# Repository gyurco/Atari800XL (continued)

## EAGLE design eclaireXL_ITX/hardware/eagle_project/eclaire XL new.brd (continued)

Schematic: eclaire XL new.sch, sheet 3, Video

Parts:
C10, C11: 0.1uF; C0805
HDMI: HDMI
JP2: JP2E; JP2
R5: 348; M0805
R6, R7, R8: 75; M0805
R9, R10: 100; R0805
RN1, RN2: 270; 743-8
S-VIDEO_COMP: MD04SS; MDIN04SS
VGA: DB15
VIDEODACSA: U5; QFP50P900X900X120-49N

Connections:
3V3: C11.1, VIDEODACSA.13 (VAA_2), VIDEODACSA.29 (VAA_3), VIDEODACSA.30 (VAA), VIDEODACSA.38 (~PSAVE); also elsewhere on the board
5V0: HDMI.18 (+5V); also elsewhere on the board
GND: C10.2, HDMI.2 (GND), HDMI.5 (GND), HDMI.8 (GND), HDMI.11 (GND), HDMI.17 (GND), HDMI.P$1 (GND), HDMI.P$2 (GND), HDMI.P$3 (GND), HDMI.P$4 (GND), R5.1, R6.1, R7.1, R8.1, S-VIDEO_COMP.1, S-VIDEO_COMP.2, VGA.5, VGA.6, VGA.7, VGA.8, VGA.10, VIDEODACSA.1 (GND_2), VIDEODACSA.2 (GND_3), VIDEODACSA.12 (~SYNC), VIDEODACSA.14 (GND_4), VIDEODACSA.15 (GND_5), VIDEODACSA.25 (GND_6), VIDEODACSA.26 (GND_7), VIDEODACSA.27 (~IOB), VIDEODACSA.31 (~IOG), VIDEODACSA.33 (~IOR), VIDEODACSA.39 (GND_8), VIDEODACSA.40 (GND); also elsewhere on the board
HSYNC: R10.1; also elsewhere on the board
unnamed: R9.2, VGA.14
unnamed: R10.2, VGA.13
unnamed: JP2.3, R6.2, VGA.1, VIDEODACSA.34 (IOR)
unnamed: R7.2, S-VIDEO_COMP.4, VGA.2, VIDEODACSA.32 (IOG)
unnamed: C10.1, VIDEODACSA.36 (VREF)
unnamed: R5.2, VIDEODACSA.37 (RSET)
unnamed: C11.2, VIDEODACSA.35 (COMP)
unnamed: HDMI.1 (TX2_P), RN1.8
unnamed: JP2.1, R8.2, VGA.3, VIDEODACSA.28 (IOB)
unnamed: HDMI.3 (TX2_N), RN1.7
unnamed: HDMI.4 (TX1_P), RN1.6
unnamed: HDMI.6 (TX1_N), RN1.5
unnamed: HDMI.7 (TX0_P), RN2.8
unnamed: HDMI.9 (TX0_N), RN2.7
unnamed: HDMI.10 (CLK_P), RN2.6
unnamed: HDMI.12 (CLK_N), RN2.5
unnamed: JP2.2, S-VIDEO_COMP.3
VGA_B0: VIDEODACSA.16 (B0); also elsewhere on the board
VGA_B1: RN2.2, VIDEODACSA.17 (B1); also elsewhere on the board
VGA_B2: VIDEODACSA.18 (B2); also elsewhere on the board
VGA_B3: VIDEODACSA.19 (B3); also elsewhere on the board
VGA_B4: RN2.1, VIDEODACSA.20 (B4); also elsewhere on the board
VGA_B5: RN2.4, VIDEODACSA.21 (B5); also elsewhere on the board
VGA_B6: RN2.3, VIDEODACSA.22 (B6); also elsewhere on the board
VGA_B7: VIDEODACSA.23 (B7); also elsewhere on the board
VGA_BLANK_N: VIDEODACSA.11 (~BLANK); also elsewhere on the board
VGA_CLK: VIDEODACSA.24 (CLOCK); also elsewhere on the board
VGA_G0: VIDEODACSA.3 (G0); also elsewhere on the board
VGA_G1: VIDEODACSA.4 (G1); also elsewhere on the board
VGA_G2: VIDEODACSA.5 (G2); also elsewhere on the board
VGA_G3: VIDEODACSA.6 (G3); also elsewhere on the board
VGA_G4: VIDEODACSA.7 (G4); also elsewhere on the board
VGA_G5: VIDEODACSA.8 (G5); also elsewhere on the board
VGA_G6: VIDEODACSA.9 (G6); also elsewhere on the board
VGA_G7: VIDEODACSA.10 (G7); also elsewhere on the board
VGA_R0: RN1.1, VIDEODACSA.41 (R0); also elsewhere on the board
VGA_R1: RN1.2, VIDEODACSA.42 (R1); also elsewhere on the board
VGA_R2: VIDEODACSA.43 (R2); also elsewhere on the board
VGA_R3: RN1.4, VIDEODACSA.44 (R3); also elsewhere on the board
VGA_R4: RN1.3, VIDEODACSA.45 (R4); also elsewhere on the board
VGA_R5: VIDEODACSA.46 (R5); also elsewhere on the board
VGA_R6: VIDEODACSA.47 (R6); also elsewhere on the board
VGA_R7: VIDEODACSA.48 (R7); also elsewhere on the board
VSYNC: R9.1; also elsewhere on the board

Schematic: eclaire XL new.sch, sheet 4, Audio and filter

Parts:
AC97_AUDIO: ML10
C21, C24: 100uF; C1206
C22, C23, C25, C26: 10nF; C0805
J3: AUDIO-JACK2CUI; AUDIO-JACK-CUI-353X
R35, R36, R37, R38: 560; M0805
R39: 1k; M0805

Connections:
AUDIO_LEFT: R38.2; also elsewhere on the board
AUDIO_RIGHT: R36.2; also elsewhere on the board
GND: AC97_AUDIO.2, C22.2, C23.2, C25.1, C26.1, J3.P$1 (SLEEVE); also elsewhere on the board
MIC_AC97: AC97_AUDIO.1; also elsewhere on the board
unnamed: C21.2, C22.1, R35.1
unnamed: C23.1, R35.2, R36.1, R39.2
unnamed: C26.2, R37.2, R38.1, R39.1
unnamed: AC97_AUDIO.9, C24.1, J3.P$2 (TIP)
unnamed: AC97_AUDIO.5, C21.1, J3.P$3 (RING)
unnamed: C24.2, C25.2, R37.1

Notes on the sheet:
Filter for delta sigma audio dac

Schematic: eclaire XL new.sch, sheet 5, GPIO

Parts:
GPIO_A: ML40E; ML40
GPIO_B: ML14
RN13, RN14, RN15, RN16, RN17, RN18, RN19, RN20, RN21, RN26, RN27, RN28: 100; 743-8
U$5: HDR_SMALL_36_DEV_LALIGNED; HDR_141_36

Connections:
3V3: GPIO_A.29, GPIO_B.13; also elsewhere on the board
5V0: GPIO_A.11, GPIO_B.14; also elsewhere on the board
EXP1: GPIO_B.1, RN26.6
EXP2: GPIO_B.2, RN26.5
EXP3: GPIO_B.3, RN27.8
EXP4: GPIO_B.4, RN27.7
EXP5: GPIO_B.5, RN27.6
EXP6: GPIO_B.6, RN27.5
EXP7: GPIO_B.7, RN28.8
EXP8: GPIO_B.8, RN28.7
EXP9: GPIO_B.9, RN28.6
EXP10: GPIO_B.10, RN28.5
GND: GPIO_A.12, GPIO_A.30, GPIO_B.11, GPIO_B.12; also elsewhere on the board
GPIOA0: RN13.1, U$5.P$1 (GPIO_0); also elsewhere on the board
GPIOA1: RN13.2, U$5.P$2 (GPIO_1); also elsewhere on the board
GPIOA2: RN13.3, U$5.P$3 (GPIO_2); also elsewhere on the board
GPIOA3: RN13.4, U$5.P$4 (GPIO_3); also elsewhere on the board
GPIOA4: RN14.1, U$5.P$5 (GPIO_4); also elsewhere on the board
GPIOA5: RN14.2, U$5.P$6 (GPIO_5); also elsewhere on the board
GPIOA6: RN14.3, U$5.P$7 (GPIO_6); also elsewhere on the board
GPIOA7: RN14.4, U$5.P$8 (GPIO_7); also elsewhere on the board
GPIOA8: RN15.1, U$5.P$9 (GPIO_8); also elsewhere on the board
GPIOA9: RN15.2, U$5.P$10 (GPIO_9); also elsewhere on the board
GPIOA10: RN15.3, U$5.P$11 (GPIO_10); also elsewhere on the board
GPIOA11: RN15.4, U$5.P$12 (GPIO_11); also elsewhere on the board
GPIOA12: RN16.1, U$5.P$13 (GPIO_12); also elsewhere on the board
GPIOA13: RN16.2, U$5.P$14 (GPIO_13); also elsewhere on the board
GPIOA14: RN16.3, U$5.P$15 (GPIO_14); also elsewhere on the board
GPIOA15: RN16.4, U$5.P$16 (GPIO_15); also elsewhere on the board
GPIOA16: RN17.1, U$5.P$17 (GPIO_16); also elsewhere on the board
GPIOA17: RN17.2, U$5.P$18 (GPIO_17); also elsewhere on the board
GPIOA18: RN17.3, U$5.P$19 (GPIO_18); also elsewhere on the board
GPIOA19: RN17.4, U$5.P$20 (GPIO_19); also elsewhere on the board
GPIOA20: RN18.1, U$5.P$21 (GPIO_20); also elsewhere on the board
GPIOA21: RN18.2, U$5.P$22 (GPIO_21); also elsewhere on the board
GPIOA22: RN18.3, U$5.P$23 (GPIO_22); also elsewhere on the board
GPIOA23: RN18.4, U$5.P$24 (GPIO_23); also elsewhere on the board
GPIOA24: RN19.1, U$5.P$25 (GPIO_24); also elsewhere on the board
GPIOA25: RN19.2, U$5.P$26 (GPIO_25); also elsewhere on the board
GPIOA26: RN19.3, U$5.P$27 (GPIO_26); also elsewhere on the board
GPIOA27: RN19.4, U$5.P$28 (GPIO_27); also elsewhere on the board
GPIOA28: RN20.1, U$5.P$29 (GPIO_28); also elsewhere on the board
GPIOA29: RN20.2, U$5.P$30 (GPIO_29); also elsewhere on the board
GPIOA30: RN20.3, U$5.P$31 (GPIO_30); also elsewhere on the board
GPIOA31: RN20.4, U$5.P$32 (GPIO_31); also elsewhere on the board
GPIOA32: RN21.1, U$5.P$33 (GPIO_32); also elsewhere on the board
GPIOA33: RN21.2, U$5.P$34 (GPIO_33); also elsewhere on the board
GPIOA34: RN21.3, U$5.P$35 (GPIO_34); also elsewhere on the board
GPIOA35: RN21.4, U$5.P$36 (GPIO_35); also elsewhere on the board
GPIOB8: RN26.1; also elsewhere on the board
GPIOB9: RN26.2; also elsewhere on the board
GPIOB10: RN26.3; also elsewhere on the board
GPIOB11: RN26.4; also elsewhere on the board
GPIOB12: RN27.1; also elsewhere on the board
GPIOB13: RN27.2; also elsewhere on the board
GPIOB14: RN27.3; also elsewhere on the board
GPIOB15: RN27.4; also elsewhere on the board
GPIOC16: RN28.2; also elsewhere on the board
GPIOC17: RN28.1; also elsewhere on the board
GPIOC18: RN28.3; also elsewhere on the board
GPIOC19: RN28.4; also elsewhere on the board
unnamed: GPIO_A.1, RN13.8
unnamed: GPIO_A.2, RN13.7
unnamed: GPIO_A.3, RN13.6
unnamed: GPIO_A.4, RN13.5
unnamed: GPIO_A.5, RN14.8
unnamed: GPIO_A.6, RN14.7
unnamed: GPIO_A.7, RN14.6
unnamed: GPIO_A.8, RN14.5
unnamed: GPIO_A.9, RN15.8
unnamed: GPIO_A.10, RN15.7
unnamed: GPIO_A.13, RN15.6
unnamed: GPIO_A.14, RN15.5
unnamed: GPIO_A.15, RN16.8
unnamed: GPIO_A.17, RN16.6
unnamed: GPIO_A.16, RN16.7
unnamed: GPIO_A.18, RN16.5
unnamed: GPIO_A.19, RN17.8
unnamed: GPIO_A.20, RN17.7
unnamed: GPIO_A.21, RN17.6
unnamed: GPIO_A.22, RN17.5
unnamed: GPIO_A.23, RN18.8
unnamed: GPIO_A.25, RN18.6
unnamed: GPIO_A.24, RN18.7
unnamed: GPIO_A.26, RN18.5
unnamed: GPIO_A.27, RN19.8
unnamed: GPIO_A.28, RN19.7
unnamed: GPIO_A.31, RN19.6
unnamed: GPIO_A.32, RN19.5
unnamed: GPIO_A.33, RN20.8
unnamed: GPIO_A.34, RN20.7
unnamed: GPIO_A.35, RN20.6
unnamed: GPIO_A.36, RN20.5
unnamed: GPIO_A.37, RN21.8
unnamed: GPIO_A.38, RN21.7
unnamed: GPIO_A.39, RN21.6
unnamed: GPIO_A.40, RN21.5
SER2: RN26.8; also elsewhere on the board
SER3: RN26.7; also elsewhere on the board

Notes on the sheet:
Resistors!!

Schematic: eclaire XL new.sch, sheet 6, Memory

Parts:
C19: 0.1uF; C0805
SDRAM: U8; TSOP54

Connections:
3V3: C19.1, SDRAM.1 (VDD), SDRAM.3 (VDDQ), SDRAM.9 (VDDQ), SDRAM.14 (VDD), SDRAM.27 (VDD), SDRAM.43 (VDDQ), SDRAM.49 (VDDQ); also elsewhere on the board
A0: SDRAM.23 (A0); also elsewhere on the board
A1: SDRAM.24 (A1); also elsewhere on the board
A2: SDRAM.25 (A2); also elsewhere on the board
A3: SDRAM.26 (A3); also elsewhere on the board
A4: SDRAM.29 (A4); also elsewhere on the board
A5: SDRAM.30 (A5); also elsewhere on the board
A6: SDRAM.31 (A6); also elsewhere on the board
A7: SDRAM.32 (A7); also elsewhere on the board
A8: SDRAM.33 (A8); also elsewhere on the board
A9: SDRAM.34 (A9); also elsewhere on the board
A10: SDRAM.22 (A10/AP); also elsewhere on the board
A11: SDRAM.35 (A11); also elsewhere on the board
A12: SDRAM.36 (A12); also elsewhere on the board
BA0: SDRAM.20 (BA0); also elsewhere on the board
BA1: SDRAM.21 (BA1); also elsewhere on the board
CAS_N: SDRAM.17 (CAS#); also elsewhere on the board
CKE: SDRAM.37 (CKE); also elsewhere on the board
CS_N: SDRAM.19 (CS#); also elsewhere on the board
DQ0: SDRAM.2 (DQ0); also elsewhere on the board
DQ1: SDRAM.4 (DQ1); also elsewhere on the board
DQ2: SDRAM.5 (DQ2); also elsewhere on the board
DQ3: SDRAM.7 (DQ3); also elsewhere on the board
DQ4: SDRAM.8 (DQ4); also elsewhere on the board
DQ5: SDRAM.10 (DQ5); also elsewhere on the board
DQ6: SDRAM.11 (DQ6); also elsewhere on the board
DQ7: SDRAM.13 (DQ7); also elsewhere on the board
DQ8: SDRAM.42 (DQ8); also elsewhere on the board
DQ9: SDRAM.44 (DQ9); also elsewhere on the board
DQ10: SDRAM.45 (DQ10); also elsewhere on the board
DQ11: SDRAM.47 (DQ11); also elsewhere on the board
DQ12: SDRAM.48 (DQ12); also elsewhere on the board
DQ13: SDRAM.50 (DQ13); also elsewhere on the board
DQ14: SDRAM.51 (DQ14); also elsewhere on the board
DQ15: SDRAM.53 (DQ15); also elsewhere on the board
GND: C19.2, SDRAM.6 (VSSQ), SDRAM.12 (VSSQ), SDRAM.28 (VSS), SDRAM.41 (VSS), SDRAM.46 (VSSQ), SDRAM.52 (VSSQ), SDRAM.54 (VSS); also elsewhere on the board
RAS_N: SDRAM.18 (RAS#); also elsewhere on the board
SDRAM_CLK: SDRAM.38 (CLK); also elsewhere on the board
SDRAM_LDQM: SDRAM.15 (LDQM); also elsewhere on the board
SDRAM_UDQM: SDRAM.39 (DQM); also elsewhere on the board
WE_N: SDRAM.16 (WE#); also elsewhere on the board

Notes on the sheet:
Standard 64 bit wide tssop 54 sram. One like de1 would be good.

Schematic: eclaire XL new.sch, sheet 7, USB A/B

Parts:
PF2: 500mA; R1206
R25, R27, R29, R31: 22; R0805
R26, R28, R30, R32: 15k; R0805
USB_A_B: ML10
X1, X3: USB-A-H

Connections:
5V0: PF2.1; also elsewhere on the board
GND: R26.2, R28.2, R30.2, R32.2, USB_A_B.7, USB_A_B.8, X1.GND, X3.GND; also elsewhere on the board
unnamed: PF2.2, USB_A_B.1, USB_A_B.2, X1.VBUS, X3.VBUS
unnamed: R25.2, R26.1, USB_A_B.5, X1.D+
unnamed: R27.2, R28.1, USB_A_B.3, X1.D-
unnamed: R29.2, R30.1, USB_A_B.6, X3.D+
unnamed: R31.2, R32.1, USB_A_B.4, X3.D-
USB1DM: R27.1; also elsewhere on the board
USB1DP: R25.1; also elsewhere on the board
USB2DM: R31.1; also elsewhere on the board
USB2DP: R29.1; also elsewhere on the board

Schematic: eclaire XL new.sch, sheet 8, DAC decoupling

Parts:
C12, C14: 0.1uF; C0805
C13: 0.01uF; C0805
C15: 10uF; C0805

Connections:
3V3: C12.1, C13.1, C14.1, C15.1; also elsewhere on the board
GND: C12.2, C13.2, C14.2, C15.2; also elsewhere on the board

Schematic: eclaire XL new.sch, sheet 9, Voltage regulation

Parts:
1.1V: U3; SOT95P280X145-5N
1V1: White; CHIP-LED0805
2.5V: U2; SOT95P280X145-5N
2V5: Green; CHIP-LED0805
3.3/2.5/1.1/GND: J2; 1X04
3.3V: U1; SOT95P280X145-5N
3V3: Red; CHIP-LED0805
C1, C2, C3, C4, C5: 10uF; C0805
C6, C7, C8: 22uF; C0805
C9: 15pF; C0805
L1, L2, L3: 1uH; L3225M
PF1: 1A; R1206
R1: 1k; R0805
R2: 4k7; R0805
R3: 200; R0805
R4: 240; R0805
R22: 82; R0805
R23, R24: 56; R0805
TR1: BC817-16LT1SMD; SOT23-BEC
U$6: MOLEX_PS

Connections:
1V1: 3.3/2.5/1.1/GND.3, C8.1, C9.1, L3.2, R4.2, TR1.B; also elsewhere on the board
2V5: 2.5V.4 (ADJ/BYP), 3.3/2.5/1.1/GND.2, C7.1, L2.2, R23.2; also elsewhere on the board
3V3: 3.3/2.5/1.1/GND.1, 3.3V.4 (ADJ/BYP), C6.1, L1.2, R22.2; also elsewhere on the board
5V0: 1.1V.1 (VIN), 1V1.A, 2.5V.1 (VIN), 3.3V.1 (VIN), C3.1, C4.1, C5.1, PF1.2, R1.1, R2.1; also elsewhere on the board
5V0FAST: 1.1V.3 (EN), C1.1, R1.2
5V0SLOW: 2.5V.3 (EN), 3.3V.3 (EN), C2.2, R2.2
GND: 1.1V.2 (GND), 2.5V.2 (GND), 2V5.C, 3.3/2.5/1.1/GND.4, 3.3V.2 (GND), 3V3.C, C1.2, C2.1, C3.2, C4.2, C5.2, C6.2, C7.2, C8.2, R3.1, R24.2, U$6.- (--); also elsewhere on the board
unnamed: PF1.1, U$6.+
unnamed: 3V3.A, R22.1
unnamed: 2V5.A, R23.1
unnamed: 1V1.C, TR1.C
unnamed: R24.1, TR1.E
unnamed: 1.1V.5 (VOUT), L3.1
unnamed: 2.5V.5 (VOUT), L2.1
unnamed: 3.3V.5 (VOUT), L1.1
unnamed: 1.1V.4 (ADJ/BYP), C9.2, R3.2, R4.1

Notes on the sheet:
TODO: RC delay calc

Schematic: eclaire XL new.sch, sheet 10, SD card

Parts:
R40, R41, R42: 47K; M0805
SD: SDSOCKET

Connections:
3V3: R40.2, R41.2, R42.2, SD.4 (3V3); also elsewhere on the board
GND: SD.3 (GND), SD.6 (GND2), SD.10 (GP1), SD.11 (GP2); also elsewhere on the board
SD_CS: R40.1, SD.1 (CS); also elsewhere on the board
SD_DAT1: SD.8 (DAT1); also elsewhere on the board
SD_DAT2: SD.9 (DAT2); also elsewhere on the board
SD_DETECT: SD.3A (CARD_DET); also elsewhere on the board
SD_MISO: R42.1, SD.7 (DATA_OUT); also elsewhere on the board
SD_MOSI: R41.1, SD.2 (DATA_IN); also elsewhere on the board
SD_SCK: SD.5 (SCLK); also elsewhere on the board
SD_WRITEPROTECT: SD.8A (WRITE_PR); also elsewhere on the board

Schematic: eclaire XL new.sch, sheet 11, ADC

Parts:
ADC: U4; SOT95P280X145-5N
C16: 0.1uF; C0805
MIC_IN_SEL: J1; JP3Q
R11, R13: 2k; M0805

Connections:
3V3: ADC.1 (VCC), C16.1, R11.1, R13.2; also elsewhere on the board
GND: ADC.2 (VSS), C16.2; also elsewhere on the board
MIC_AC97: MIC_IN_SEL.2; also elsewhere on the board
MIC_IN: ADC.3 (AIN), MIC_IN_SEL.1, MIC_IN_SEL.3, MIC_IN_SEL.5
MIC_PBI: MIC_IN_SEL.6; also elsewhere on the board
MIC_SIO: MIC_IN_SEL.4; also elsewhere on the board
SCL: ADC.5 (SCL), R11.2; also elsewhere on the board
SDA: ADC.4 (SDA), R13.1; also elsewhere on the board

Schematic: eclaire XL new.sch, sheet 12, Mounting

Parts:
H1, H2, H3, H4, H5, H6, H7: MOUNT-PAD-ROUND3.6; 3,6-PAD

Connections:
GND: H1.B3,6, H2.B3,6, H3.B3,6, H4.B3,6, H5.B3,6, H6.B3,6, H7.B3,6; also elsewhere on the board

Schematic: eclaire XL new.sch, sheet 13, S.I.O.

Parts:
C20: 0.1uF; C0805K
D1: 1N4148; SOD123
PF3: 500mA; R1206
QS3384: U9; TSSOP24
R33, R34: 2k7; M0805
RN3, RN4: 100; 743-8
RN5, RN6: 4K7; 743-8
S.I.O._INTERFACE: ML10
TR2: MOT; SOT23-BEC

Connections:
5V0: D1.2 (AN), R33.1, RN5.1, RN5.2, RN5.3, RN5.4, RN6.1, RN6.2, RN6.3, RN6.4, TR2.E; also elsewhere on the board
COMMAND: RN4.2; also elsewhere on the board
GND: C20.2, QS3384.1 (BE), QS3384.12 (GND), QS3384.13 (BE), QS3384.20 (B), QS3384.21 (A), QS3384.22 (A), QS3384.23 (B); also elsewhere on the board
MIC_SIO: S.I.O._INTERFACE.9; also elsewhere on the board
MOTOR_RAW: RN3.1; also elsewhere on the board
unnamed: QS3384.3 (A), RN3.8
unnamed: QS3384.19 (B), RN5.6, S.I.O._INTERFACE.2
unnamed: QS3384.4 (A), RN3.7
unnamed: QS3384.7 (A), RN3.6
unnamed: QS3384.8 (A), RN3.5
unnamed: QS3384.11 (A), RN4.8
unnamed: QS3384.18 (A), RN4.7
unnamed: QS3384.17 (A), RN4.6
unnamed: QS3384.14 (A), RN4.5
unnamed: R34.2, TR2.B
unnamed: QS3384.16 (B), RN5.8, S.I.O._INTERFACE.4
unnamed: QS3384.15 (B), RN6.6, S.I.O._INTERFACE.6
unnamed: QS3384.10 (B), RN6.7, S.I.O._INTERFACE.7
unnamed: QS3384.9 (B), RN6.5, S.I.O._INTERFACE.5
unnamed: QS3384.6 (B), RN5.7, S.I.O._INTERFACE.3
unnamed: PF3.2, TR2.C
unnamed: QS3384.5 (B), RN5.5, S.I.O._INTERFACE.1
unnamed: QS3384.2 (B), R33.2, R34.1
unnamed: C20.1, D1.1 (CA), QS3384.24 (4V3)
unnamed: PF3.1, S.I.O._INTERFACE.8, S.I.O._INTERFACE.10
PROCEED: RN4.3; also elsewhere on the board
SIO_CLOCKIN: RN4.4; also elsewhere on the board
SIO_CLOCKOUT: RN3.2; also elsewhere on the board
SIO_IN: RN3.3; also elsewhere on the board
SIO_IRQ: RN3.4; also elsewhere on the board
SIO_OUT: RN4.1; also elsewhere on the board

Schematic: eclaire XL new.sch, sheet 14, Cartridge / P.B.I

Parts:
C38, C39, C40, C41: 0.1uF; C0805K
D3: 1N4148; SOD123
IC1: U14; TSSOP24
IC2: U15; TSSOP24
IC3: U16; TSSOP24
IC4: U17; TSSOP24
P.B.I._INTERFACE: ML40E; ML40
R50, R51: 10k; M0805
R52, R53, R54, R55: 4k7; M0805
RN29, RN30, RN31, RN32, RN33, RN34, RN35, RN36, RN37: 100; 743-8

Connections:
4V3_INT: C38.1, C39.1, C40.1, C41.1, D3.1 (CA), IC1.24 (4V3), IC2.24 (4V3), IC3.24 (4V3), IC4.24 (4V3)
5V0: D3.2 (AN), R52.1, R53.1, R54.1, R55.1; also elsewhere on the board
.A0: IC3.2 (B), P.B.I._INTERFACE.23
.A1: IC3.6 (B), P.B.I._INTERFACE.25
.A2: IC3.10 (B), P.B.I._INTERFACE.27
.A3: IC3.15 (B), P.B.I._INTERFACE.28
.A4: IC3.9 (B), P.B.I._INTERFACE.26
.A5: IC3.5 (B), P.B.I._INTERFACE.24
.A6: IC2.23 (B), P.B.I._INTERFACE.22
.A7: IC2.19 (B), P.B.I._INTERFACE.20
.A8: IC2.15 (B), P.B.I._INTERFACE.18
.A9: IC2.9 (B), P.B.I._INTERFACE.16
.A10: IC1.10 (B), P.B.I._INTERFACE.5
.A11: IC1.15 (B), P.B.I._INTERFACE.6
.A12: IC2.5 (B), P.B.I._INTERFACE.14
.A13: IC3.23 (B), P.B.I._INTERFACE.34
.A14: IC4.2 (B), P.B.I._INTERFACE.35
.A15: IC4.5 (B), P.B.I._INTERFACE.36
.CCTL_N: IC1.2 (B), P.B.I._INTERFACE.1
.D0: IC2.2 (B), P.B.I._INTERFACE.13
.D1: IC2.6 (B), P.B.I._INTERFACE.15
.D2: IC2.10 (B), P.B.I._INTERFACE.17
.D3: IC1.23 (B), P.B.I._INTERFACE.10
.D4: IC2.20 (B), P.B.I._INTERFACE.21
.D5: IC2.16 (B), P.B.I._INTERFACE.19
.D6: IC1.20 (B), P.B.I._INTERFACE.9
.D7: IC1.19 (B), P.B.I._INTERFACE.8
.EXTSEL_N: IC3.20 (B), P.B.I._INTERFACE.33, R52.2
.IRQ_N: IC4.10 (B), P.B.I._INTERFACE.39, R55.2
.MPD_N: IC4.6 (B), P.B.I._INTERFACE.37, R53.2
.PHI2: IC1.5 (B), P.B.I._INTERFACE.2
.RD4: IC3.16 (B), P.B.I._INTERFACE.31, R51.2
.RD5: IC1.6 (B), P.B.I._INTERFACE.3, R50.2
.REF_N: IC4.9 (B), P.B.I._INTERFACE.38, R54.2
.RST_N: IC4.15 (B), P.B.I._INTERFACE.40
.RW_N: IC1.9 (B), P.B.I._INTERFACE.4
.S4_N: IC3.19 (B), P.B.I._INTERFACE.32
.S5_N: IC1.16 (B), P.B.I._INTERFACE.7
GND: C38.2, C39.2, C40.2, C41.2, IC1.1 (BE), IC1.12 (GND), IC1.13 (BE), IC2.1 (BE), IC2.12 (GND), IC2.13 (BE), IC3.1 (BE), IC3.12 (GND), IC3.13 (BE), IC4.1 (BE), IC4.12 (GND), IC4.13 (BE), IC4.16 (B), IC4.17 (A), IC4.18 (A), IC4.19 (B), IC4.20 (B), IC4.21 (A), IC4.22 (A), IC4.23 (B), R50.1, R51.1; also elsewhere on the board
GPIOB16: RN30.1; also elsewhere on the board
GPIOB17: RN30.2; also elsewhere on the board
GPIOB18: RN30.3; also elsewhere on the board
GPIOB19: RN30.4; also elsewhere on the board
GPIOB20: RN31.1; also elsewhere on the board
GPIOB21: RN31.2; also elsewhere on the board
GPIOB22: RN31.3; also elsewhere on the board
GPIOB23: RN31.4; also elsewhere on the board
GPIOB24: RN32.1; also elsewhere on the board
GPIOB25: RN32.2; also elsewhere on the board
GPIOB26: RN32.3; also elsewhere on the board
GPIOB27: RN32.4; also elsewhere on the board
GPIOB28: RN33.1; also elsewhere on the board
GPIOB29: RN33.2; also elsewhere on the board
GPIOB30: RN33.3; also elsewhere on the board
GPIOB31: RN33.4; also elsewhere on the board
GPIOB32: RN34.1; also elsewhere on the board
GPIOB33: RN34.2; also elsewhere on the board
GPIOB34: RN34.3; also elsewhere on the board
GPIOB35: RN34.4; also elsewhere on the board
GPIOC20: RN29.1; also elsewhere on the board
GPIOC21: RN29.2; also elsewhere on the board
GPIOC22: RN29.3; also elsewhere on the board
GPIOC23: RN29.4; also elsewhere on the board
GPIOC24: RN35.1; also elsewhere on the board
GPIOC25: RN35.2; also elsewhere on the board
GPIOC26: RN35.3; also elsewhere on the board
GPIOC27: RN35.4; also elsewhere on the board
GPIOC28: RN36.1; also elsewhere on the board
GPIOC29: RN36.2; also elsewhere on the board
GPIOC30: RN36.3; also elsewhere on the board
GPIOC31: RN36.4; also elsewhere on the board
GPIOC32: RN37.1; also elsewhere on the board
GPIOC33: RN37.2; also elsewhere on the board
GPIOC34: RN37.3; also elsewhere on the board
GPIOC35: RN37.4; also elsewhere on the board
MIC_PBI: P.B.I._INTERFACE.29, P.B.I._INTERFACE.30; also elsewhere on the board
PIO1: IC1.3 (A), RN29.8
PIO2: IC1.4 (A), RN29.7
PIO3: IC1.7 (A), RN29.6
PIO4: IC1.8 (A), RN29.5
PIO5: IC1.11 (A), RN30.8
PIO6: IC1.14 (A), RN30.7
PIO7: IC1.17 (A), RN30.6
PIO8: IC1.18 (A), RN30.5
PIO9: IC1.21 (A), RN31.8
PIO10: IC1.22 (A), RN31.7
PIO11: IC2.3 (A), RN31.6
PIO12: IC2.4 (A), RN31.5
PIO13: IC2.7 (A), RN32.8
PIO14: IC2.8 (A), RN32.7
PIO15: IC2.11 (A), RN32.6
PIO16: IC2.14 (A), RN32.5
PIO17: IC2.17 (A), RN33.8
PIO18: IC2.18 (A), RN33.7
PIO19: IC2.21 (A), RN33.6
PIO20: IC2.22 (A), RN33.5
PIO21: IC3.3 (A), RN34.8
PIO22: IC3.4 (A), RN34.7
PIO23: IC3.7 (A), RN34.6
PIO24: IC3.8 (A), RN34.5
PIO25: IC3.11 (A), RN35.8
PIO26: IC3.14 (A), RN35.7
PIO27: IC3.17 (A), RN35.6
PIO28: IC3.18 (A), RN35.5
PIO29: IC3.21 (A), RN36.8
PIO30: IC3.22 (A), RN36.7
PIO31: IC4.3 (A), RN36.6
PIO32: IC4.4 (A), RN36.5
PIO33: IC4.7 (A), RN37.8
PIO34: IC4.8 (A), RN37.7
PIO35: IC4.11 (A), RN37.6
PIO36: IC4.14 (A), RN37.5

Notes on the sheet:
PBI CONNECTOR

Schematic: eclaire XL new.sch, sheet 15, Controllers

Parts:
74HCT03: U12; SO14
C28, C29A, C30A: 0.1uF; C0805K
C29, C30, C31, C32: 0.047uF; C0805K
D2: 1N4148; SOD123
IC5: U10; TSSOP24
JOY1: JOYSTICK1; M09HP
JOY2: JOYSTICK2; M09HP
LM339: U11; TSSOP-14
PF4: 500mA; R1206
R43, R44: 4.7k; M0805
R45: 1.2K; R0805
R46: 2.1K; R0805
RN7, RN10, RN12: 4K7; 743-8
RN8, RN9: 220; 743-8
RN11: 1K; 743-8
RN22, RN23, RN24, RN25: 100; 743-8

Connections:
3V3: R45.2, RN12.5, RN12.6, RN12.7, RN12.8; also elsewhere on the board
4V3_INT1: C28.2, D2.1 (CA), IC5.24 (4V3)
5V0: 74HCT03.14 (VCC), C29A.1, C30A.1, D2.2 (AN), LM339.3 (VCC), PF4.1, R43.2, R44.2, RN7.1, RN7.2, RN7.3, RN7.4, RN10.5, RN10.6, RN10.7, RN10.8; also elsewhere on the board
5V00: JOY1.7, JOY2.7, PF4.2
GND: 74HCT03.7 (GND), C28.1, C29.2, C29A.2, C30.2, C30A.2, C31.2, C32.2, IC5.1 (BE), IC5.12 (GND), IC5.13 (BE), JOY1.8, JOY2.8, LM339.12 (GND), R46.1; also elsewhere on the board
GPIOB0: RN24.1; also elsewhere on the board
GPIOB1: RN24.2; also elsewhere on the board
GPIOB2: RN24.3; also elsewhere on the board
GPIOB3: RN24.4; also elsewhere on the board
GPIOB4: RN25.1; also elsewhere on the board
GPIOB5: RN25.2; also elsewhere on the board
GPIOB6: RN25.3; also elsewhere on the board
GPIOB7: RN25.4; also elsewhere on the board
GPIOC8: RN22.1; also elsewhere on the board
GPIOC9: RN22.2; also elsewhere on the board
GPIOC10: RN22.3; also elsewhere on the board
GPIOC11: RN22.4; also elsewhere on the board
GPIOC12: RN23.1; also elsewhere on the board
GPIOC13: RN23.3; also elsewhere on the board
GPIOC14: RN23.2; also elsewhere on the board
GPIOC15: RN23.4; also elsewhere on the board
JIO1: IC5.3 (A), RN22.8
JIO2: IC5.4 (A), RN22.7
JIO3: IC5.7 (A), RN22.6
JIO4: IC5.8 (A), RN22.5
JIO5: IC5.11 (A), RN23.8
JIO6: IC5.21 (A), RN23.6
JIO7: IC5.22 (A), RN23.7
JIO8: IC5.18 (A), RN23.5
JIO9: IC5.17 (A), RN24.8
JIO10: IC5.14 (A), RN24.7
JIO11: LM339.1 (OUT), RN12.1, RN24.6
JIO12: LM339.2 (OUT), RN12.2, RN24.5
JIO13: LM339.14 (OUT), RN12.3, RN25.8
JIO14: LM339.13 (OUT), RN12.4, RN25.7
JIO15: 74HCT03.1 (I0), 74HCT03.2 (I1), 74HCT03.4 (I0), 74HCT03.5 (I1), 74HCT03.9 (I0), 74HCT03.10 (I1), 74HCT03.12 (I0), 74HCT03.13 (I1), RN25.6
unnamed: LM339.4 (-IN), LM339.6 (-IN), LM339.8 (-IN), LM339.10 (-IN), R45.1, R46.2
PORTA0: IC5.2 (B), RN7.5, RN8.4
PORTA1: IC5.5 (B), RN7.6, RN8.3
PORTA2: IC5.6 (B), RN7.7, RN8.2
PORTA3: IC5.9 (B), RN7.8, RN8.1
PORTA4: IC5.10 (B), RN9.4, RN10.1
PORTA5: IC5.15 (B), RN9.3, RN10.2
PORTA6: IC5.16 (B), RN9.2, RN10.3
PORTA7: IC5.19 (B), RN9.1, RN10.4
PORTA_PROT0: JOY1.1, RN8.5
PORTA_PROT1: JOY1.2, RN8.6
PORTA_PROT2: JOY1.3, RN8.7
PORTA_PROT3: JOY1.4, RN8.8
PORTA_PROT4: JOY2.1, RN9.5
PORTA_PROT5: JOY2.2, RN9.6
PORTA_PROT6: JOY2.3, RN9.7
PORTA_PROT7: JOY2.4, RN9.8
POT0: 74HCT03.3 (O), C29.1, LM339.5 (+IN), RN11.1
POT1: 74HCT03.6 (O), C30.1, LM339.7 (+IN), RN11.2
POT2: 74HCT03.8 (O), C32.1, LM339.9 (+IN), RN11.4
POT3: 74HCT03.11 (O), C31.1, LM339.11 (+IN), RN11.3
POTIN0: JOY1.9, RN11.7
POTIN1: JOY1.5, RN11.8
POTIN2: JOY2.9, RN11.5
POTIN3: JOY2.5, RN11.6
SER1: RN25.5; also elsewhere on the board
TRIG0: IC5.23 (B), JOY1.6, R43.1
TRIG1: IC5.20 (B), JOY2.6, R44.1

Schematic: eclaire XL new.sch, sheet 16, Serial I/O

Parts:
C33, C34, C35, C36: 1UF; C0805K
MAX232: U13; SO16L
R47, R48, R49: 330; M0805
RX: LEDCHIP-LED0805; CHIP-LED0805
TX: LEDCHIP-LED0805; CHIP-LED0805
X2: F09V

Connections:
3V3: MAX232.16 (VCC), RX.A, TX.A; also elsewhere on the board
GND: C34.2, C36.2, MAX232.15 (GND), X2.5; also elsewhere on the board
unnamed: R47.1, TX.C
unnamed: R48.1, RX.C
unnamed: C34.1, MAX232.2 (V+)
unnamed: C33.2, MAX232.3 (C1-)
unnamed: C35.2, MAX232.5 (C2-)
unnamed: C33.1, MAX232.1 (C1+)
unnamed: C35.1, MAX232.4 (C2+)
unnamed: C36.1, MAX232.6 (V-)
unnamed: MAX232.14 (T1OUT), X2.2
unnamed: MAX232.13 (R1IN), X2.3
unnamed: MAX232.7 (T2OUT), X2.8
unnamed: MAX232.12 (R1OUT), R48.2, R49.2
SER1: MAX232.10 (T2IN); also elsewhere on the board
SER2: MAX232.11 (T1IN), R47.2; also elsewhere on the board
SER3: R49.1; also elsewhere on the board

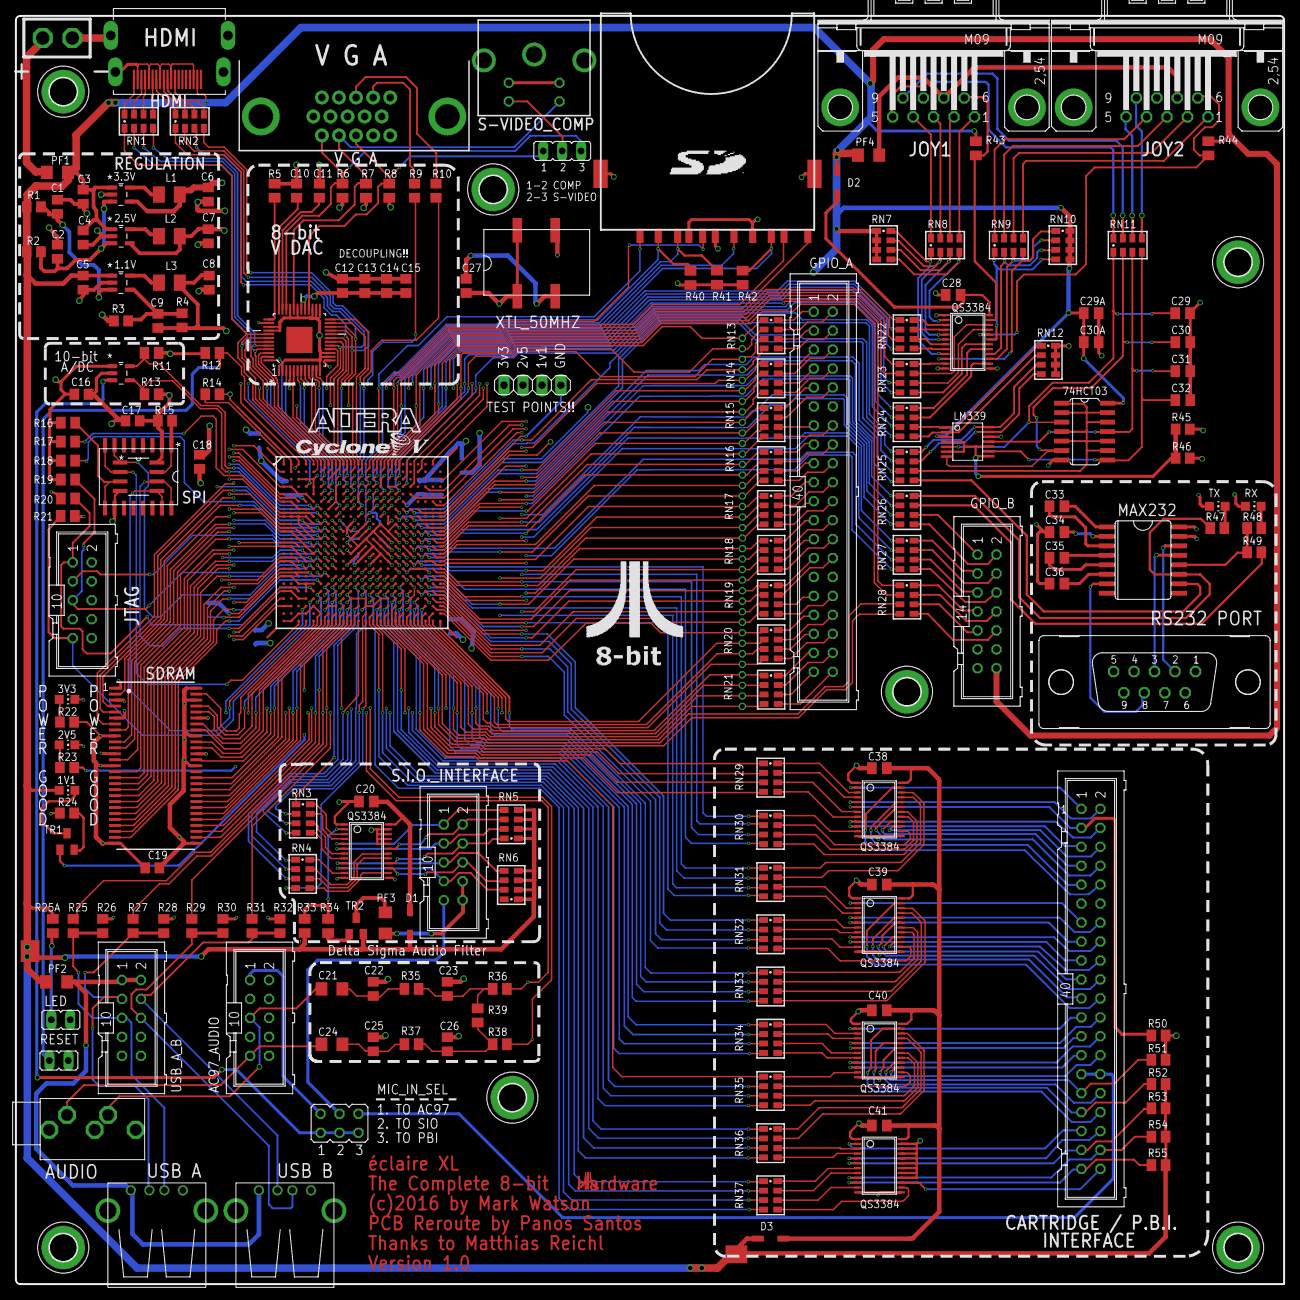
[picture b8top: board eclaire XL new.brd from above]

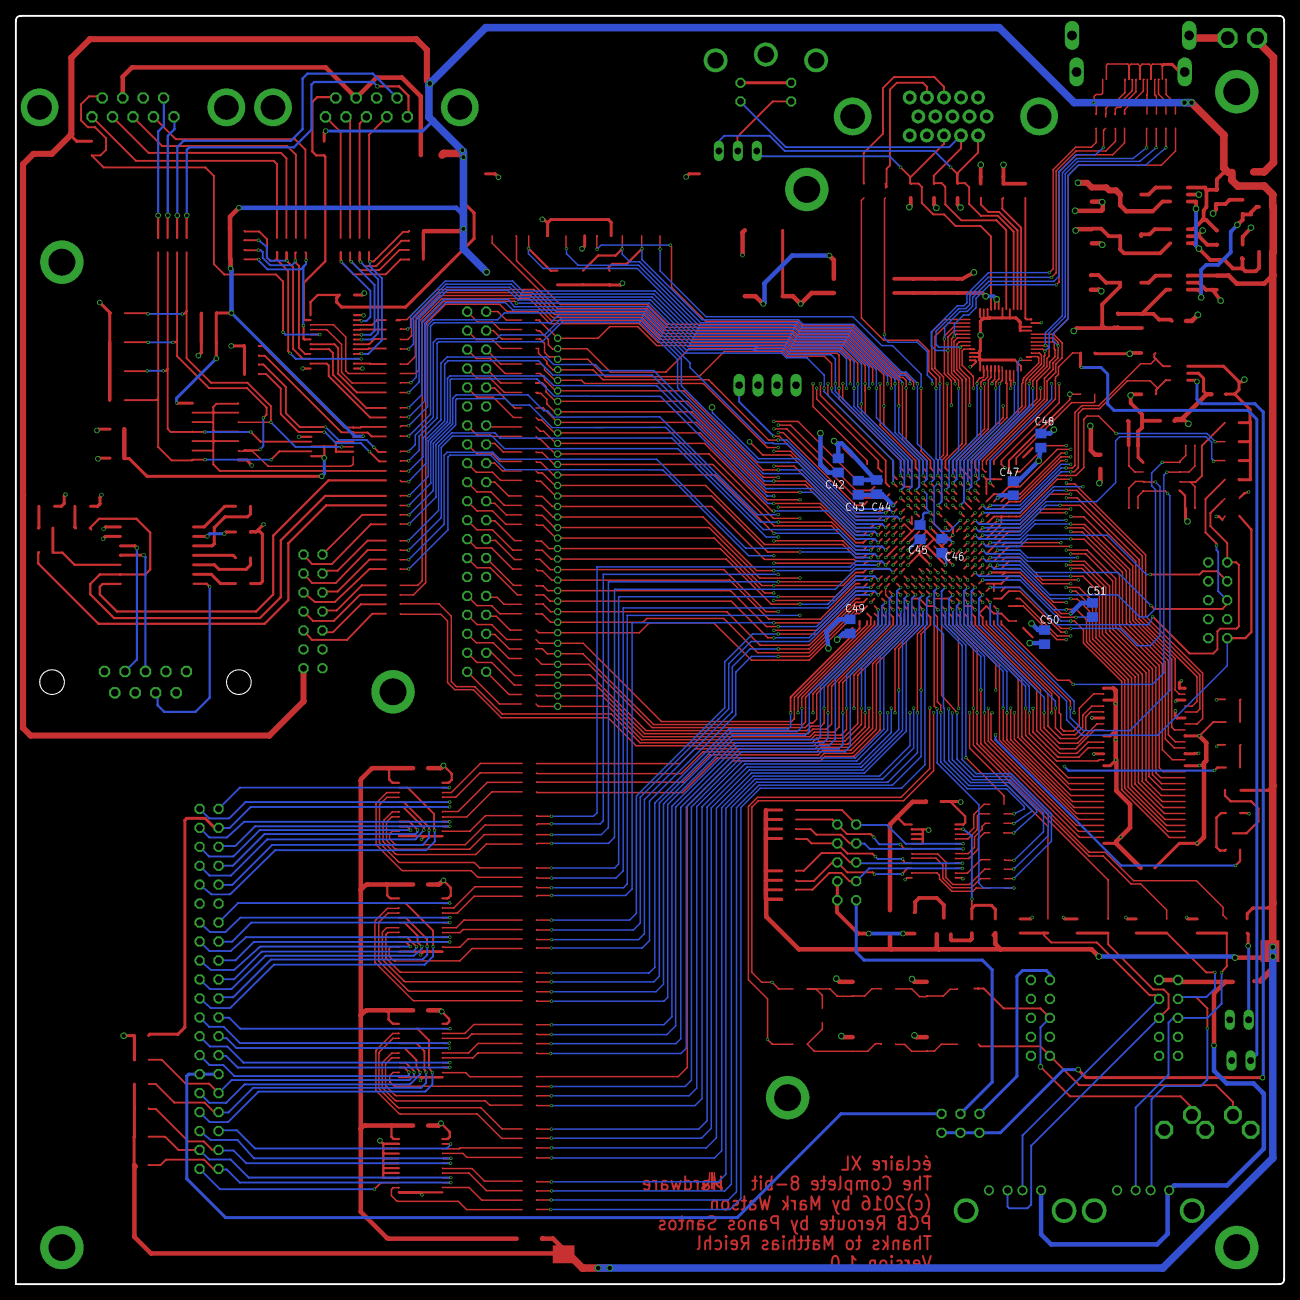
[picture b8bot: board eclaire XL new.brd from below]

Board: 4 copper layers, 170.0 x 170.0 mm, 211 parts (10 on the bottom side), 453 nets.

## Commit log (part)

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2020-05-16 Convert to signed maths
2020-05-16 1 bit too many
2020-05-17 Fix Q and cutoff to better match 8580
2020-05-18 Fix filter clipping with Jammer songs!
2020-05-20 Some overflow issues
2020-05-24 Turn off full
2020-05-24 Added 2nd order sigma delta
2020-05-24 Remove quad psg covox
2020-05-25 Updated version
2020-05-25 Sigma delta was correct before
2020-05-25 Missing comma
2020-05-30 Correct edge bit. Also interrupt 1 should still work in output mode.
2020-06-01 Added sychronizer to pia
2020-06-01 Fix pia interrupts cleared on other edge!
2020-06-02 Make acid test pass again, while still having fujinet work
2020-06-13 First cut of flash support. Synthesizes but not tested.
2020-06-13 sensitivity list mistake
2020-06-14 Big fix for intel ip, apparently the read addressing is broken!
2020-06-14 Debugged flash reading. Added read of detect right.
2020-06-14 Update version due to flash support
2020-06-15 Add access to the CFM as well, so that we can flash from Respeqt
2020-06-15 Added a simple tool to create a core to flash. Also added a program to extra the core from pokeymax and save to disk - start of a flash program/config editor.
2020-06-16 Added menu and options - still needs some debugging
2020-06-17 Fix truncation problem at high pokey volume with quad pokey
2020-06-17 Build core.bin for all targets
2020-06-17 Flasher binary
2020-06-17 Missing version
2020-06-20 Examples/tools for flashing with openocd
2020-06-20 Added full core for v2 as a test - needs CS1 mod. Generate svf for openocd flashing
2020-06-23 Increased version
2020-06-23 Initialize pokeycfg from regs instead of flash
2020-06-23 Changed right detection logic to xor on all bits, was failing for covox playing which do not toggle bits 5 downto 0
2020-06-26 Debugged in sim
2020-06-27 Allow 1 bit more for saturation!
2020-06-27 Split out the mixer, will reduce its logic usage next
2020-06-28 Cut sid size slightly by sharing pre-filter adder
2020-06-28 Missed init
2020-07-03 Reimplement mixer to cut some more LEs, it now adds a channel at a time to a shared accum
2020-07-12 Missed from sensitivity list
2020-07-12 First cut of sample player support, so far only played sawtooth on one channel but it is alive!
2020-07-17 Debugging adpcm: nibble back to front, reset logic incorrect. More to come...
2020-07-18 Verified in isim
2020-07-19 Make syncreset work on any cycle
2020-07-19 gone
2020-07-20 16-bit samples from sample module, doubled sample clock to match Paula
2020-07-21 Cap on overflow
2020-07-22 Debugged IMA mode
2020-07-24 Wired up sample player to rom for adpcm table and made it compile
2020-07-24 Add step table to rom init image.
2020-07-25 Fix noise on loading from covox (we), add more bits to len.
2020-07-27 Fit some clock domain timing issues with flash controller use
2020-07-27 Fix when to store samples from dma or cpu
2020-07-28 Read sid filter params from flash. Seems to work on quad sid, but not on full - needs debugging!
2020-07-29 Added real 6581 and 8580 filter curves (not switchable yet). Use 16-bit to store them to save rom space
2020-07-29 Suppress step dma when adpcm not enabled
2020-07-31 Added some notes and invatigation into 6581 filters, making use of the best emulation resources.
2020-08-16 6581/8580 sid mode in config. 6581 is still very basic: fitler curve and no distortion
2020-08-16 Changed to single bit and missed these
2020-08-16 Use correct filter for 8580
2020-08-16 Wrong size
2020-09-02 Missing default
2020-09-03 Add external sid and psg clock support, so I can run it in sync with real chips
2020-09-26 Speed up keyboard scanning and fix order - this should fix AKI (but need to test). As for TK2, might be tricky...
2020-09-26 Restrict support
2020-09-26 Add psg curves
2020-09-26 latch by accident
2020-09-26 Starvation fix
2020-09-26 PSG at wrong address - typo!!
2020-09-27 Statevariable rom fetch -> generic rom fetch state machine (foundation)
2020-09-28 Add sid wave form to pof+bin after core and update checksum
2020-09-28 Added the captued sid waves (Can capture own later but these should be ok...)
2020-09-28 Use real sid waveforms
2020-09-30 Put 1/Q into rom, with values for 8580 and 6581
2020-10-01 Make pokey mixer request from flash only when needed
2020-10-02 Fix a few errors in the state maching, it was not making requests to flash!
2020-10-02 Keep request active until done. Got to correct on completion!
2020-10-02 Use real keyboard scan at 1.5MHz i2c clock, for tkii compatibility
2020-10-03 Fix force break - when cleared break no longer forced. Only an issue really when there is no clock, as in certain tape turbo solutions.
2020-10-03 Blank modify, no sid in 02 or 04
2020-10-04 Add more headroom to keyboard scan for TKII (allow int to be later and speed up scan allowing for later int in the cycle)
2020-10-06 IRQ after copying initial data to buffer
2020-10-08 Fix data nibble used for 4-bit mode
2020-10-12 Using a different clock speed for the sigma delta helps with whistling! Need a v2c of hardware really to cut the noise...
2020-10-31 Better handling for TKII, still not 100% but possible to type now!
2020-11-05 SIDMAX v1!
2020-11-06 Add stereo sid. Improve config program display.
2020-11-10 No longer used
2020-11-14 Setup for 10M16, more changes required but this allow a build
2020-12-16 10M16 flash support
2020-12-19 Updated sigmoid to convient range
2020-12-19 Corrected clock frequency
2020-12-19 f distortion for 6581
2020-12-19 Disable distortion on 8580
2020-12-19 Cut f and distortion precision to make it almost fit in 10M08!
2020-12-19 Rescaled lookup
2020-12-20 Cut area by sharing some parts of envelope. Now JUST fits in v2 with area reduction turned on.
2020-12-20 Typo: wrong lfsr
2020-12-20 Refreshed sid c64 vhd from patch
2020-12-21 Only distort on +ve, now sounding closer...
2020-12-22 SID does not drive the bus when write only or non-decoded registers are read
2021-01-01 Switch to more accurate clock generator, though with jitter. No longer fits on v2, need to find more space!
2021-01-01 Change state machine style so that quartus recognises them, I do not use explicit bit patterns
2021-01-01 Change state machine style to one quartus understands
2021-01-09 Disable, not enough space on v2 full
2021-01-09 Added stereo sid, added 10M04 of the 7800 build
2021-01-09 Fix main envelope and wave timings vs 6581, few scenarios were tested on audiotest board vs a real chip. Add DC offset which is required for sample support. On amplitude modulator in 6581 and on ext 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
2021-01-09 Add basic digifix support (8580D... means 8580 with digifix)
2021-01-09 Make digifix clearer
2021-01-10 Enable better sid/psg clock support. In order to fit everything into 10M08 had to disable audout2 and change some flash parameters (need verifying)
2021-01-10 This is in fact needed...
2021-01-10 Fixed a few bugs, causing a short final block
2021-01-10 Too small (at least until I remove pokey entirely...)
2021-01-10 Refreshed
2021-01-13 Wrapping burst mode non-functional. Reported to Intel. Reverting for now.
2021-01-13 Allow restarting on failure
2021-01-19 Add verify support. Page erase after sector erase fix.
2021-01-24 Add MiST OSD, cart loading from OSD, fix PLL switching
2021-01-25 MiST: add atari800mode
2021-01-28 MiST: use the ARM CPU to handle disk files
2021-01-29 MiST: disable PLL switching during ROM downloading
    Fixes the initial ROM download
2021-02-02 dual pokey option
    Disable dual pokey for pseudo-stereo
2021-02-06 Missing cof file, meant no arg file created for the release
2021-02-06 Reset ps2 after pll change in case of stuck keys
2021-02-07 Mistification from slingshot, many many many thanks!
2021-02-07 Add pull-ups on triggers(gtia has internal pull-up). Improve colour resolution.
2021-02-09 Use schmit trigger for SID and BCLK inputs
2021-02-09 Remove SIO_IN2/3
2021-04-01 Allow umounting disks from the OSD
2021-09-01 Test driven SID improvements
2021-09-01 Bug fix
2021-09-01 SIDMAX
2021-09-16 This seems to break v3 flashing, reverting for now
2021-09-19 Tighten up some timings.
2021-09-19 Remove flash for 02, basically too large to fit ANYWHERE!
2021-09-19 Missing from sensitivity
2021-09-19 _ can be in var...
2021-09-21 Two tone reset suppresses the pulse
2021-09-23 Add disable support for each audio output. Split config screen into pages since it was getting too long!
2021-09-29 Update to work with latest stuff from pokeymax
2021-09-29 Moved pokey to own folder
2022-03-18 Writes still allowed when disabled!
2022-03-18 Corrected config access value and number of covox registers
2022-06-16 Add a .gitignore
2022-11-23 MiST: add paddle enable/disable option
2023-02-27 Fix for 10M08 not reading reliably since >=1.24
2023-02-27 Bumped version
2023-03-27 Add 10M16 mono, handy for debugging
2023-03-27 Added wide delay line for register delays
2023-12-04 SiDi128: add HDMI output, use mist-modules
2023-12-06 ioctl_addr is the last written address, not the size
2024-01-22 Allow to disable custom hires mode in Antic
2024-03-10 Only poll clock at sensible times
2024-03-18 Fix non-paddle mode
2024-03-29 Added sidmax schematic
2024-03-29 Pure digital 40 pin chip. Needs 5v and gnd wiring on, then can be 6502, antic (I do not have this working yet) or gtia
2024-04-08 Added mountsmd files
2024-04-08 Renumbering left it called pokeymax1
2024-04-09 Added 4 layer version. Just with a polygon fill of 3.3v and GND. Reason: drill size needs 4 layer with jlcpcb
2024-04-09 Not a gerber!
2024-04-17 First cut of pokeymaxv4 core, untested as yet and probably some mistakes. Might also have broken v2/v3, need to test they still build/work
2024-04-23 Added missing lvds
2024-04-28 Mix ADC in
2024-04-28 Do not feed back SIO noise if using the ADC, since we will have it from that. Allows playing stereo tapes as mono through the 1010 otherwise the analog tracks comes in as digital noise!
2024-05-17 Correct audio outputs, I got them back to front on the board design
2024-06-03 Improve AN sample timing
2024-06-12 Added 10M02 stereo version for v4
2024-08-31 Improving timing by registering on the input
2024-08-31 Sensitivity list missing some entries
2024-08-31 Mixer interface changed slightly
2024-08-31 Add wide delay line
2024-09-01 Correct offsets again
2024-09-02 Switch to single script to add the sid wave data, with automatic offsets
2024-09-02 Rest of ip upgrade to q23
2024-09-02 Add other sigmadelta clock
2024-09-02 Split into a block per version. Generate code automatically since I was getting worse and worse. Some clearly overlap. Automatic offsets for patching wave data into CFM. Generate core.bin from svf bl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
2024-09-02 v2 is not a special version any more with new build script
2024-09-02 Back to front. Added missing tool too!
2024-09-04 Corrected dir name. Fix the parameter passing to the qsf!
2024-09-05 Pad core.bin out to the actual flash size. Correct version parameter.
2024-09-05 Updated sidcfg. To keep it in sync just use one set of code with a few ifdefs.
2024-09-05 This fix does not see needed any more on 08, but does on 16. It fails to read it otherwise.
2024-09-05 Put the flash ip back, the old ip seems better!
2024-09-05 For some reason the M16 core turns write protect on after erasing some sectors. Guess: Perhaps some sectors do not exist on some device and in error case it protects itself?
2024-09-05 Some names clash in the hash. Add an extra layer. Also if sidwavedataneeded the value is blank, not zero. So the pof creation fails!
2024-09-05 Fix for 10M16 flash
2024-12-07 Flip sign for spdif. When adc silenced revert back to mixing sio data a bit.
2024-12-08 Added volume for SIO DATA and ADC
2024-12-08 Add some unused stuff to the qsf
2024-12-08 Added another file needed to build
2024-12-10 This is not the right fix. Investing then will commit the right fix.
2024-12-10 Missing comment
2024-12-14 Added audio signal detector
